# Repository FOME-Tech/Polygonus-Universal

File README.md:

# Polygonus-Universal

Basic pinout for the bosch 88 pin plug intended for universal use.  

## NOT COMPATIBLE WITH ANY PNP APPLICATION  

## NOTE - 88pin plug is now hard to source as it seems to be NLA from Aliexpress. 
Hardware tested ok on the first fabrication but is now obsolete due to connector sourcing issues. 
Board is provided as is for reference of if someone wants to fabricate and source their own connectors.

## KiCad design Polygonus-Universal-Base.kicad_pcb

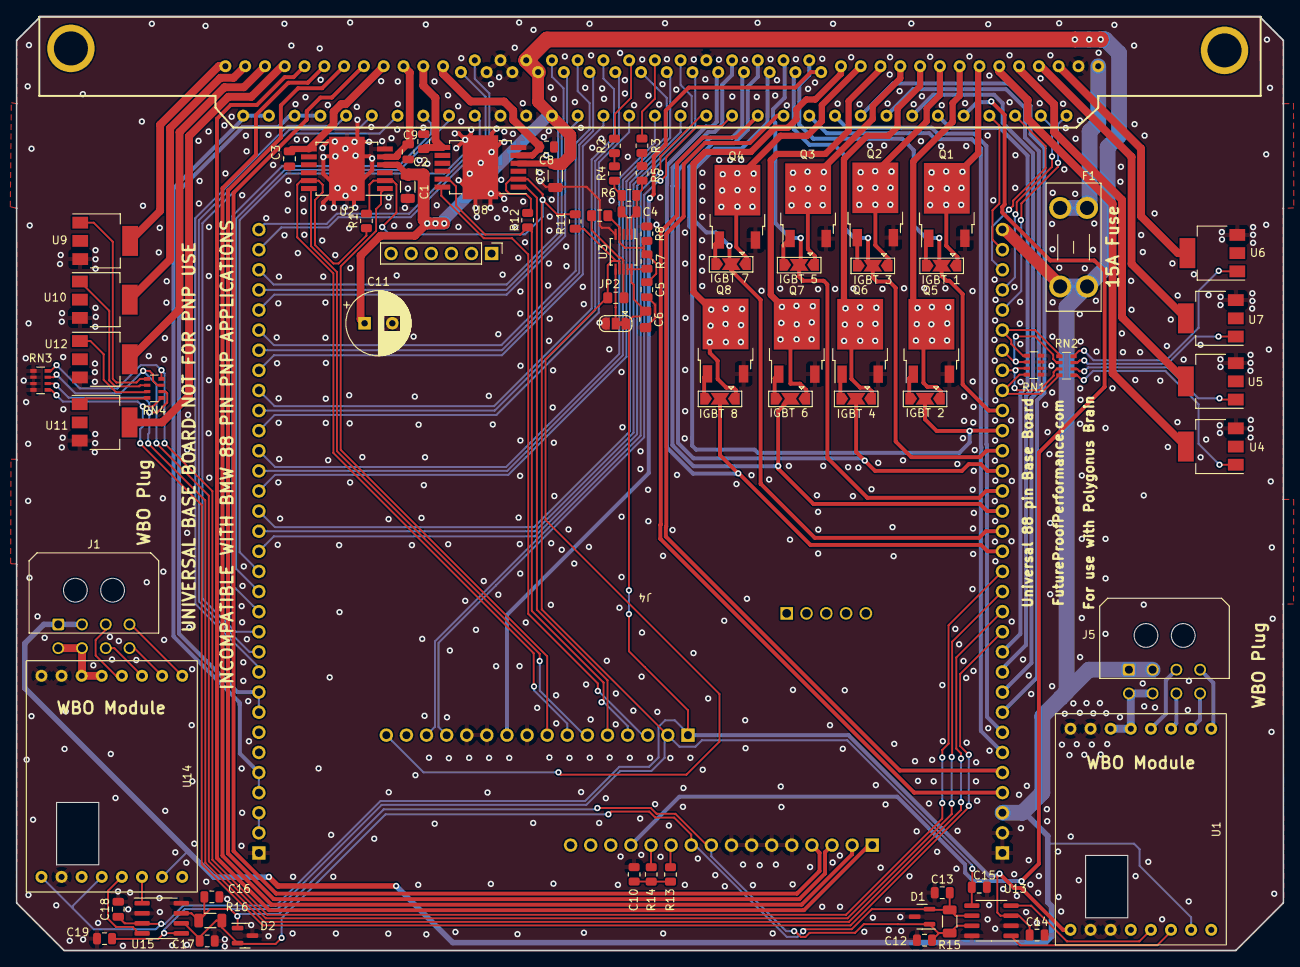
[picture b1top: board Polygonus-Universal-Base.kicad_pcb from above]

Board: 2 copper layers, 160.0 x 118.0 mm, 78 parts (0 on the bottom side), 138 nets.

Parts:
C1, C7: 10u; C_1206_3216Metric
C2, C3, C8, C9: 10n; C_0805_2012Metric
C4: 1n; C_0805_2012Metric
C5: 1u; C_0805_2012Metric
C6: 100n; C_0805_2012Metric_Pad1.18x1.45mm_HandSolder
C10: 1u; R_0805_2012Metric
C11: 56u; CP_Radial_D8.0mm_P3.50mm
C12, C13, C16, C17: 47p; C_0805_2012Metric
C14, C15, C18, C19: 100n; C_0805_2012Metric
D1, D2: NUP2105L; SOT-23
F1: Fuse; Fuseholder_Blade_Mini_Keystone_3568
J1, J5: Conn_02x04_Top_Bottom; Molex_Micro-Fit_3.0_43045-0800_2x04_P3.00mm_Horizontal
J4: Polygonus_Plugs; Polygonus-With-USB-SWD
JP1, JP3, JP4, JP5, JP6, JP7, JP8, JP9: Jumper_3_Open; SolderJumper-3_P2.0mm_Open_TrianglePad1.0x1.5mm
JP2: Jumper_3_Bridged12; SolderJumper-3_P1.3mm_Bridged12_RoundedPad1.0x1.5mm
Motronic_88pin1: Motronic_88pin; 88Pin Motronic BMW
Q1, Q2, Q3, Q4, Q5, Q6, Q7, Q8: NGD8201AN; TO-252-2
R1, R12: 10k; R_0805_2012Metric
R2, R3, R4, R5, R11: 4.7k; R_0805_2012Metric
R6, R13, R14: DNP; R_0805_2012Metric
R7, R8: 1k; R_0805_2012Metric
R9, R10: DNP; R_0805_2012Metric_Pad1.15x1.40mm_HandSolder
R15, R16: 120; R_1206_3216Metric
RN1, RN2, RN3, RN4: 1k; R_Array_Convex_4x0603
U1, U14: f042_wideband_module
U2, U8: TLE9201SG; Infineon_PG-DSO-12-9
U3: MAX9924; MSOP-10_3x3mm_P0.5mm
U4, U5, U6, U7, U9, U10, U11, U12: VNL5090; SOT-223
U13, U15: TJA1051T-3; SOIC-8_3.9x4.9mm_P1.27mm

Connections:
+3.3V: C15.1, C19.1, J4.82, R1.2, R11.1, R12.2, U2.2 (VSO), U8.2 (VSO), U13.5 (VIO), U15.5 (VIO)
+5V: C6.1, C14.1, C18.1, J4.81, JP2.1 (A), R7.1, U1.1 (5V), U3.9 (INT_THRS), U3.10 (VCC), U13.3 (VCC), U14.1 (5V), U14.4 (SEL_2), U15.3 (VCC)
/5V_SENSOR_1: J4.40, J4.41, Motronic_88pin1.58, Motronic_88pin1.59
/5V_SENSOR_2: J4.36, J4.37, Motronic_88pin1.56, Motronic_88pin1.57
/12V_KEY: J4.90, Motronic_88pin1.21
/12V_MR: F1.1, Motronic_88pin1.28
/12V_MR_FUSE: C1.2, C7.2, C11.1, F1.2, J1.1, J1.2, J4.3, J4.32, J5.1, J5.2, Motronic_88pin1.10, Motronic_88pin1.37, Motronic_88pin1.68, U1.7 (VBatt_Sense), U2.4 (VS), U8.4 (VS), U14.7 (VBatt_Sense)
/12V_PROT: J4.34, J4.35
/AT1: J4.51, Motronic_88pin1.15
/AT2: J4.50, Motronic_88pin1.73
/AT3: J4.49, Motronic_88pin1.43
/AT4: J4.48, Motronic_88pin1.16
/AV1: J4.62, Motronic_88pin1.38
/AV2: J4.61, Motronic_88pin1.11
/AV3: J4.60, Motronic_88pin1.69
/AV4: J4.59, Motronic_88pin1.39
/AV5: J4.58, Motronic_88pin1.12
/AV6: J4.57, Motronic_88pin1.70
/AV7: J4.56, Motronic_88pin1.40
/AV8: J4.55, Motronic_88pin1.13
/AV9: J4.54, Motronic_88pin1.71
/AV10: J4.53, Motronic_88pin1.72
/AV11: J4.52, Motronic_88pin1.14
/CAN2+: C12.2, C16.2, D1.1 (K), D2.1 (K), J4.73, R15.1, R16.1, U13.7 (CANH), U15.7 (CANH)
/CAN2-: C13.1, C17.1, D1.2 (K), D2.2 (K), J4.74, R15.2, R16.2, U13.6 (CANL), U15.6 (CANL)
/CAN+: J4.93, Motronic_88pin1.75
/CAN-: J4.94, Motronic_88pin1.74
/CAN_RX: U1.5 (CAN_RX), U13.4 (RXD)
/CAN_RX2: U14.5 (CAN_RX), U15.4 (RXD)
/CAN_TX: U1.6 (CAN_TX), U13.1 (TXD)
/CAN_TX2: U14.6 (CAN_TX), U15.1 (TXD)
/CRANK +: Motronic_88pin1.41, R2.2
/CRANK -: Motronic_88pin1.42, R3.2
/DIGITAL_1: J4.47, Motronic_88pin1.65
/DIGITAL_2: J4.46, Motronic_88pin1.64
/DIGITAL_3: J4.45, Motronic_88pin1.63
/DIGITAL_4: J4.44, Motronic_88pin1.62
/DIGITAL_5: J4.43, Motronic_88pin1.61
/DIGITAL_6: J4.42, Motronic_88pin1.60
/ETB1_+: C8.2, Motronic_88pin1.34, U8.5 (OUT1)
/ETB1_-: C9.1, Motronic_88pin1.6, U8.7 (OUT2)
/ETB1_DIR: J4.85, U8.1 (DIR)
/ETB1_DIS: J4.84, R12.1, U8.11 (DIS)
/ETB1_PWM: J4.83, U8.12 (PWM)
/ETB2_+: C2.2, Motronic_88pin1.33, U2.5 (OUT1)
/ETB2_-: C3.1, Motronic_88pin1.5, U2.7 (OUT2)
/ETB2_DIR: J4.88, U2.1 (DIR)
/ETB2_DIS: J4.87, R1.1, U2.11 (DIS)
/ETB2_PWM: J4.86, U2.12 (PWM)
/ExtraLSA: Motronic_88pin1.1, U9.4 (Drain)
/ExtraLSB: Motronic_88pin1.29, U10.4 (Drain)
/ExtraLSC: Motronic_88pin1.2, U12.4 (Drain)
/ExtraLSD: Motronic_88pin1.30, U11.4 (Drain)
/HS1: J4.68, Motronic_88pin1.32
/HS2: J4.67, Motronic_88pin1.4
/HS3: J4.66, Motronic_88pin1.31
/HS4: J4.65, Motronic_88pin1.3
/HeaterNeg: J5.5, J5.6, U1.11 (HEATER-), U1.12 (HEATER-)
/HeaterNeg2: J1.5, J1.6, U14.11 (HEATER-), U14.12 (HEATER-)
/IGBT1: JP1.1 (A), Motronic_88pin1.25, Q1.2 (C)
/IGBT2: JP6.1 (A), Motronic_88pin1.52, Q5.2 (C)
/IGBT3: JP3.1 (A), Motronic_88pin1.24, Q2.2 (C)
/IGBT4: JP7.1 (A), Motronic_88pin1.51, Q6.2 (C)
/IGBT5: JP4.1 (A), Motronic_88pin1.23, Q3.2 (C)
/IGBT6: JP8.1 (A), Motronic_88pin1.50, Q7.2 (C)
/IGBT7: JP5.1 (A), Motronic_88pin1.22, Q4.2 (C)
/IGBT8: JP9.1 (A), Motronic_88pin1.49, Q8.2 (C)
/IGN1: J4.23, JP1.2 (C), Motronic_88pin1.48
/IGN2: J4.22, JP6.2 (C), Motronic_88pin1.46
/IGN3: J4.21, JP3.2 (C), Motronic_88pin1.20
/IGN4: J4.20, JP7.2 (C), Motronic_88pin1.18
/IGN5: J4.19, JP4.2 (C), Motronic_88pin1.47
/IGN6: J4.18, JP8.2 (C), Motronic_88pin1.45
/IGN7: J4.17, JP5.2 (C), Motronic_88pin1.19
/IGN8: J4.16, JP9.2 (C), Motronic_88pin1.17
/IGN9: J4.15, RN3.8 (R1.2), RN4.4 (R4.1)
/IGN10: J4.14, RN3.7 (R2.2), RN4.3 (R3.1)
/IGN11: J4.13, RN3.6 (R3.2), RN4.2 (R2.1)
/IGN12: J4.12, RN3.5 (R4.2), RN4.1 (R1.1)
/KNOCK_1: J4.63, Motronic_88pin1.35
/KNOCK_2: J4.64, Motronic_88pin1.7
/LS1: J4.4, Motronic_88pin1.76
/LS2: J4.5, Motronic_88pin1.77
/LS3: J4.6, Motronic_88pin1.78
/LS4: J4.7, Motronic_88pin1.79
/LS5: J4.8, Motronic_88pin1.80
/LS6: J4.9, Motronic_88pin1.81
/LS7: J4.10, Motronic_88pin1.82
/LS8: J4.11, Motronic_88pin1.83
/LS9: J4.24, RN1.8 (R1.2), RN2.4 (R4.1)
/LS9ADD: Motronic_88pin1.53, U4.4 (Drain)
/LS10: J4.25, RN1.7 (R2.2), RN2.3 (R3.1)
/LS10ADD: Motronic_88pin1.26, U5.4 (Drain)
/LS11: J4.26, RN1.6 (R3.2), RN2.2 (R2.1)
/LS11ADD: Motronic_88pin1.54, U7.4 (Drain)
/LS12: J4.27, RN1.5 (R4.2), RN2.1 (R1.1)
/LS12ADD: Motronic_88pin1.27, U6.4 (Drain)
/LS13: J4.28, Motronic_88pin1.88
/LS14: J4.29, Motronic_88pin1.87
/LS15: J4.30, Motronic_88pin1.86
/LS16: J4.31, Motronic_88pin1.85
/LSU_Ip: J5.3, U1.13 (LSU_ip)
/LSU_Ip2: J1.3, U14.13 (LSU_ip)
/LSU_Rtrim: J5.8, U1.15 (LSU_rtrim)
/LSU_Rtrim2: J1.8, U14.15 (LSU_rtrim)
/LSU_Un: J5.4, U1.16 (LSU_un)
/LSU_Un2: J1.4, U14.16 (LSU_un)
/LSU_Vm: J5.7, U1.14 (LSU_vm)
/LSU_Vm2: J1.7, U14.14 (LSU_vm)
/Perm_Live: J4.77, Motronic_88pin1.84
/RC1: J4.75, R13.2
/RC2: J4.76, R14.2
/VR1+: J4.96, R10.1, R11.2, U3.7 (COUT)
GND: C1.1, C2.1, C3.2, C5.2, C6.2, C7.1, C8.1, C9.2, C10.2, C11.2, C12.1, C13.2, C14.2, C15.2, C16.1, C17.2, C18.2, C19.2, D1.3 (A), D2.3 (A), J4.1, J4.2, J4.33, J4.69, J4.70, J4.71, J4.72, J4.89, J4.91, J4.92, JP2.3 (B), Motronic_88pin1.8, Motronic_88pin1.9, Motronic_88pin1.36, Motronic_88pin1.44, Motronic_88pin1.55, Motronic_88pin1.66, Motronic_88pin1.67, Q1.3 (E), Q2.3 (E), Q3.3 (E), Q4.3 (E), Q5.3 (E), Q6.3 (E), Q7.3 (E), Q8.3 (E), R8.1, RN1.1 (R1.1), RN1.2 (R2.1), RN1.3 (R3.1), RN1.4 (R4.1), RN3.1 (R1.1), RN3.2 (R2.1), RN3.3 (R3.1), RN3.4 (R4.1), U1.2 (GND), U1.3 (SEL_1), U1.9 (HEAT_GND), U1.10 (HEAT_GND2), U2.6 (GND), U2.13 (GND), U3.5 (GND), U4.3 (Source), U5.3 (Source), U6.3 (Source), U7.3 (Source), U8.6 (GND), U8.13 (GND), U9.3 (Source), U10.3 (Source), U11.3 (Source), U12.3 (Source), U13.2 (GND), U13.8 (S), U14.2 (GND), U14.9 (HEAT_GND), U14.10 (HEAT_GND2), U15.2 (GND), U15.8 (S)
unnamed: C10.1, R13.1, R14.1
unnamed: JP1.3 (B), Q1.1 (G)
unnamed: JP2.2 (C), U3.6 (ZERO_EN)
unnamed: JP3.3 (B), Q2.1 (G)
unnamed: JP4.3 (B), Q3.1 (G)
unnamed: JP5.3 (B), Q4.1 (G)
unnamed: JP6.3 (B), Q5.1 (G)
unnamed: JP7.3 (B), Q6.1 (G)
unnamed: JP8.3 (B), Q7.1 (G)
unnamed: JP9.3 (B), Q8.1 (G)
unnamed: R2.1, R4.2
unnamed: R3.1, R5.2
unnamed: RN2.8 (R1.2), U6.1 (Input)
unnamed: RN2.7 (R2.2), U7.1 (Input)
unnamed: RN2.6 (R3.2), U5.1 (Input)
unnamed: RN2.5 (R4.2), U4.1 (Input)
unnamed: RN4.8 (R1.2), U11.1 (Input)
unnamed: RN4.7 (R2.2), U12.1 (Input)
unnamed: RN4.6 (R3.2), U10.1 (Input)
unnamed: RN4.5 (R4.2), U9.1 (Input)
unnamed: C5.1, R7.2, R8.2, R9.2, U3.4 (BIAS)
unnamed: R9.1, R10.2, U3.8 (EXT)
unnamed: C4.2, R5.1, R6.1, U3.1 (IN+)
unnamed: C4.1, R4.1, R6.2, U3.2 (IN-)

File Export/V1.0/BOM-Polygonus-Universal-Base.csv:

Comment,Designator,Footprint,LCSC
TLE9201SG,"U2,U8",Infineon_PG-DSO-12-9,C112633
10u,"C1,C7",C_1206_3216Metric,C13585
MAX9924,U3,MSOP-10_3x3mm_P0.5mm,C143633
47p,"C12,C13,C16,C17",C_0805_2012Metric,C14857
NGD8201AN,"Q1,Q2,Q3,Q4,Q5,Q6,Q7,Q8",TO-252-2,C151649
10n,"C2,C3,C8,C9",C_0805_2012Metric,C1710
10k,"R1,R12",R_0805_2012Metric,C17414
1k,"R7,R8",R_0805_2012Metric,C17513
4.7k,"R11,R2,R3,R4,R5",R_0805_2012Metric,C17673
1k,"RN1,RN2,RN3,RN4",R_Array_Convex_4x0603,C20197
VNL5090,"U10,U11,U12,U4,U5,U6,U7,U9",SOT-223,C2680415
1u,"C5,C6",C_0805_2012Metric,C28323
NUP2105L,"D1,D2",SOT-23,C284104
TJA1051T-3,"U13,U15",SOIC-8_3.9x4.9mm_P1.27mm,C38695
1n,C4,C_0805_2012Metric,C46653
100n,"C14,C15,C18,C19",C_0805_2012Metric,C49678
Fuse,F1,Fuseholder_Blade_Mini_Keystone_3568,C5249699
D_Schottky,"D501,D502,D503,D504,D701,D702,D703,D704",D_SMA,C8678
56u,C11,CP_Radial_D8.0mm_P3.50mm,
1u,C10,R_0805_2012Metric,

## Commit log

2023-02-14 Stripped board in prep for layout
2023-02-14 Made the board
2023-02-14 Competed board
2023-04-29 upgraded
2023-10-05 Modified IGBTs and routed smart coils
2023-10-20 updated and fixed, check JLC exports
2023-10-22 All fixed up for JLC
2023-10-22 Moved folders and added schematics or die
2023-10-23 Fixed 12V_RAW and added grounds for sensors
2023-10-23 convert to kicad7, add jumpers for direct drive igbt output
2023-10-23 tweak silk
2023-10-23 silkscreen/erc tweaks
2023-10-23 fix labels in schematic
2023-10-23 wideband symbol/footprint
2023-10-23 fix wideband library, ERC, DRC
2023-10-23 Update design rules for JLC 4 layer
2023-10-23 4-layer-ify the board, do some rerouting for 4 layer goodness
2023-10-24 Add freewheel diodes, power pins explanation comment
2023-10-24 silkscreen cleanup
2023-10-24 route widebands to main connector
2023-10-24 adjust silkscreen label for igbts
2023-10-25 silkscreen
2023-10-31 Real minor tidy up around 12v/lowsides
2023-11-01 Fixed WBO pin allocation
2023-11-01 Added DRV8825 footprint
2023-11-02 Went over vias, did a DRC
2023-11-02 adjusted a couple of parameters to suit JLC
2023-11-02 default set HS
2023-11-02 ignore lock files
2023-11-02 stepper ls direct to logic pins
2023-11-12 export cleanup
2023-11-12 production files v1.0
2023-11-12 schematic title blocks
2023-11-19 Revert "updates"
    This reverts commit 8b03831b9e3606a0c51971a3414fde57c991d853.
2023-11-22 Removed the alleged via and 2 redundant schematic tags
2023-11-29 Fixed the vias and ran a quick DRC
    Only silk screen overlaps and complaints about the IGBT and stepper selection footprints remain, I don't think this is critical, just warnings.
2024-01-14 fixed stepper pullup and updated silkscreen
2024-01-14 Generated V2.0 Gerbs for prototype order
2024-11-27 Removed fab files to prevent YOLO orders, added note to readme.
